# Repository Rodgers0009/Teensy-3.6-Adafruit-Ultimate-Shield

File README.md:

# Teensy-3.6-Adafruit-Ultimate-Shield
Shield for the Teensy 3.6 and Adafruit Ultimate V3 GPS with interactions with all pins on the Teensy

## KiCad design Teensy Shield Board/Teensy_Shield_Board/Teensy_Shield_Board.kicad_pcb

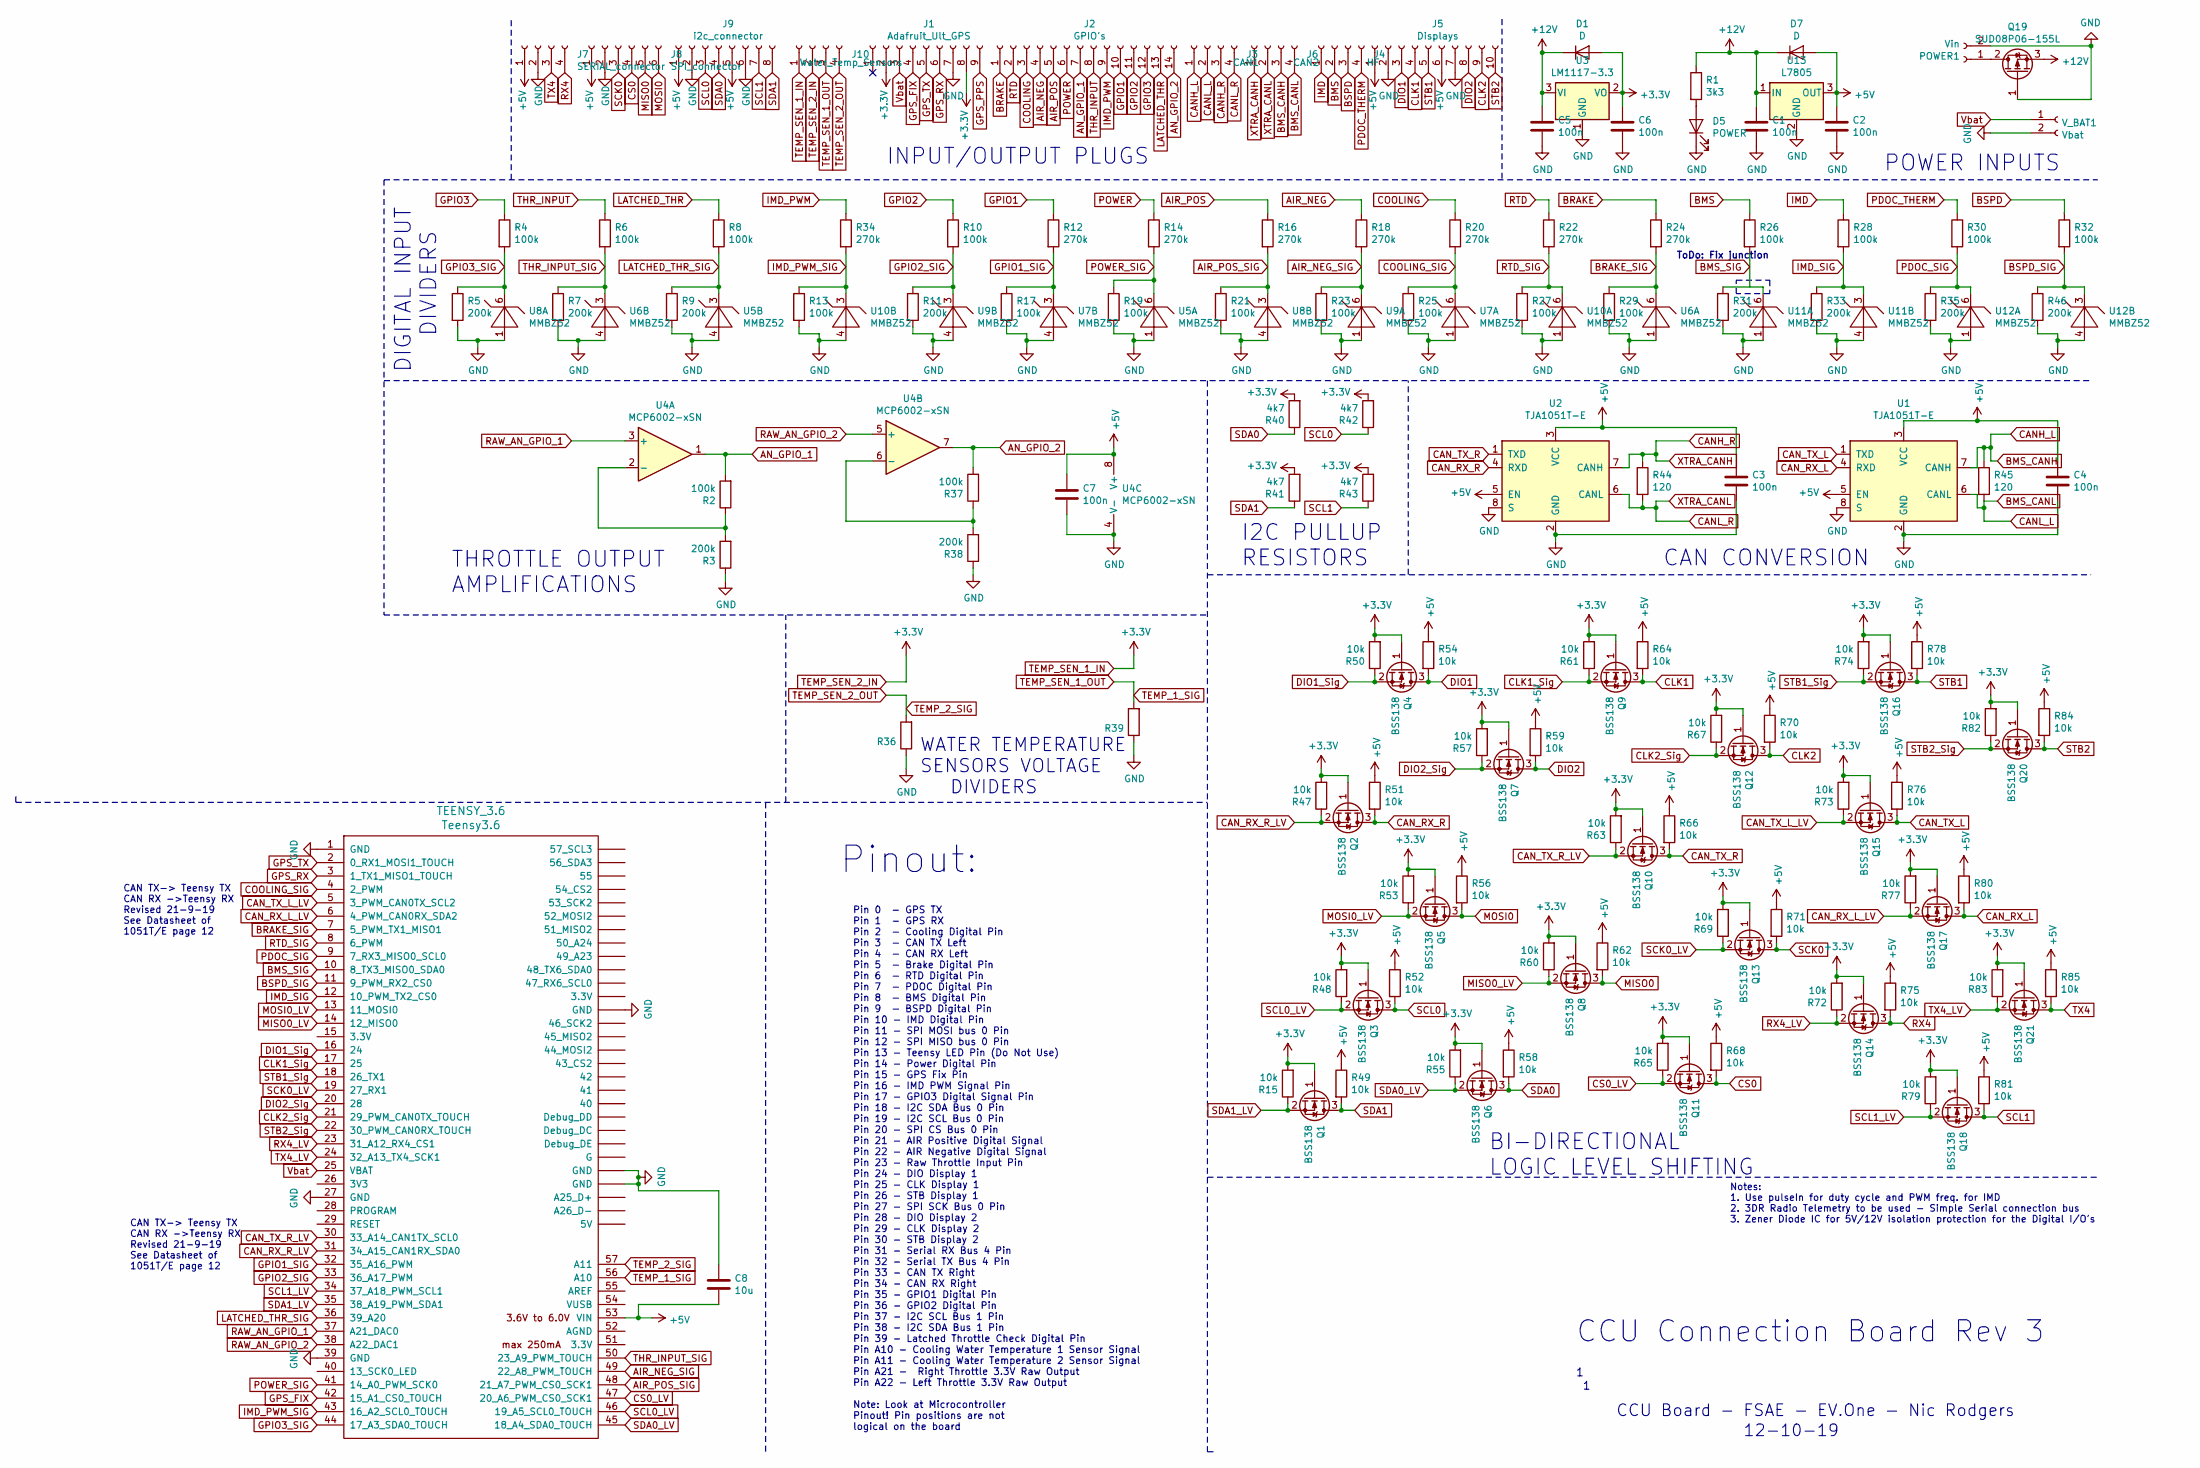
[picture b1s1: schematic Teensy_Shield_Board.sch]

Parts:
C1, C2, C3, C4, C5, C6, C7: 100n; C_0805_2012Metric
C8: 10u; C_0805_2012Metric
D1, D7: D; D_SMA
D5: POWER; LED_0805_2012Metric
J1: Adafruit_Ult_GPS; Adafruit_Ultimate_GPS
J2: GPIO's; Molex-Mini-Fit-Jr-14-pin-P4.2mm-RowP4.2mm
J3: CAN1; Molex-Mini-Fit-Jr-4-pin-P4.2mm-RowP4.2mm
J4: HF; Molex-Mini-Fit-Jr-4-pin-P4.2mm-RowP4.2mm
J5: Displays; Molex-Mini-Fit-Jr-10-pin-P4.2mm-RowP4.2mm
J6: CAN2; Molex-Mini-Fit-Jr-4-pin-P4.2mm-RowP4.2mm
J7: SERIAL_connector; Molex-Mini-Fit-Jr-4-pin-P4.2mm-RowP4.2mm
J8: SPI_connector; Molex-Mini-Fit-Jr-6-pin-P4.2mm-RowP4.2mm
J9: i2c_connector; Molex-Mini-Fit-Jr-8-pin-P4.2mm-RowP4.2mm
J10: Water_Temp_Sensors; Molex-Mini-Fit-Jr-4-pin-P4.2mm-RowP4.2mm
POWER1: Vin; Molex_MiniFit-JR-5556-02A_2x01x4.20mm_Straight
Q1, Q2, Q3, Q4, Q5, Q6, Q7, Q8, Q9, Q10, Q11, Q12, Q13, Q14, Q15, Q16, Q17, Q18, Q20, Q21: BSS138; SOT-23
Q19: SUD08P06-155L; SOT-23
R1: 3k3; R_1206_3216Metric
R2, R4, R6, R8, R10, R13, R17, R19, R21, R23, R25, R26, R27, R28, R29, R30, R32, R37: 100k; R_1206_3216Metric
R3, R5, R7, R9, R11, R31, R33, R35, R38, R46: 200k; R_1206_3216Metric
R12, R14, R16, R18, R20, R22, R24, R34: 270k; R_1206_3216Metric
R15, R47, R48, R49, R50, R51, R52, R53, R54, R55, R56, R57, R58, R59, R60, R61, R62, R63, R64, R65, R66, R67, R68, R69, R70, R71, R72, R73, R74, R75, R76, R77, R78, R79, R80, R81, R82, R83, R84, R85: 10k; R_1206_3216Metric
R36, R39: TO_BE_PROVISIONED; R_1206_3216Metric
R40, R41, R42, R43: 4k7; R_1206_3216Metric
R44, R45: 120; R_1206_3216Metric
TEENSY_3.6: Teensy3.6; Teensy35_36
U1, U2: TJA1051T-E; SOIC-8_3.9x4.9mm_P1.27mm
U3: LM1117-3.3; SOT-223
U4: MCP6002-xSN; SOIC-8_3.9x4.9mm_P1.27mm
U5, U6, U7, U8, U9, U10, U11, U12: MMBZ52; SOT-363_SC-70-6
U13: L7805; TO-263-3_TabPin2
V_BAT1: Vbat; 2032_Batt_holder

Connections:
+5V: C2.1, C3.1, C4.1, C7.1, C8.2, D7.2 (A), J5.1, J5.6, J7.1, J8.1, J9.1, J9.5, R49.1, R51.1, R52.1, R54.1, R56.1, R58.1, R59.1, R62.1, R64.1, R66.1, R68.1, R70.1, R71.1, R75.1, R76.1, R78.1, R80.1, R81.1, R84.1, R85.1, TEENSY_3.6.53 (VIN), U1.3 (VCC), U1.5 (EN), U2.3 (VCC), U2.5 (EN), U4.8 (V+), U13.3 (OUT)
+12V: C1.1, C5.1, D1.1 (K), D7.1 (K), Q19.3 (S), R1.1, U3.3 (VI), U13.1 (IN)
AIR_NEG: J2.4, R18.1
AIR_NEG_SIG: R18.2, R23.1, TEENSY_3.6.49 (22_A8_PWM_TOUCH), U9.6
AIR_POS: J2.5, R16.1
AIR_POS_SIG: R16.2, R21.1, TEENSY_3.6.48 (21_A7_PWM_CS0_SCK1), U8.3
AN_GPIO_1: J2.7, R2.2, U4.1
AN_GPIO_2: J2.14, R37.2, U4.7
BMS: J4.2, R26.1
BMS_CANH: J3.1, J6.3, R45.1, U1.7 (CANH)
BMS_CANL: J3.2, J6.4, R45.2, U1.6 (CANL)
BMS_SIG: R26.2, TEENSY_3.6.10 (8_TX3_MISO0_SDA0)
BRAKE: J2.1, R24.1
BRAKE_SIG: R24.2, R29.1, TEENSY_3.6.7 (5_PWM_TX1_MISO1), U6.6
BSPD: J4.3, R32.1
BSPD_SIG: R32.2, R46.1, TEENSY_3.6.11 (9_PWM_RX2_CS0), U12.3
CANH_R: J3.3, J6.1, R44.1, U2.7 (CANH)
CANL_R: J3.4, J6.2, R44.2, U2.6 (CANL)
CAN_RX_L: Q17.3 (D), R80.2, U1.4 (RXD)
CAN_RX_L_LV: Q17.2 (S), R77.1, TEENSY_3.6.6 (4_PWM_CAN0RX_SDA2)
CAN_RX_R: Q2.3 (D), R51.2, U2.4 (RXD)
CAN_RX_R_LV: Q2.2 (S), R47.1, TEENSY_3.6.31 (34_A15_CAN1RX_SDA0)
CAN_TX_L: Q15.3 (D), R76.2, U1.1 (TXD)
CAN_TX_L_LV: Q15.2 (S), R73.1, TEENSY_3.6.5 (3_PWM_CAN0TX_SCL2)
CAN_TX_R: Q10.3 (D), R66.2, U2.1 (TXD)
CAN_TX_R_LV: Q10.2 (S), R63.1, TEENSY_3.6.30 (33_A14_CAN1TX_SCL0)
CLK1: J5.4, Q9.3 (D), R64.2
CLK1_Sig: Q9.2 (S), R61.1, TEENSY_3.6.17 (25)
CLK2: J5.9, Q12.3 (D), R70.2
CLK2_Sig: Q12.2 (S), R67.1, TEENSY_3.6.21 (29_PWM_CAN0TX_TOUCH)
COOLING: J2.3, R20.1
COOLING_SIG: R20.2, R25.1, TEENSY_3.6.4 (2_PWM), U7.6
CS0: J8.4, Q11.3 (D), R68.2
CS0_LV: Q11.2 (S), R65.1, TEENSY_3.6.47 (20_A6_PWM_CS0_SCK1)
DIO1: J5.3, Q4.3 (D), R54.2
DIO1_Sig: Q4.2 (S), R50.1, TEENSY_3.6.16 (24)
DIO2: J5.8, Q7.3 (D), R59.2
DIO2_Sig: Q7.2 (S), R57.1, TEENSY_3.6.20 (28)
GND: C1.2, C2.2, C3.2, C4.2, C5.2, C6.2, C7.2, C8.1, D5.1 (K), J1.7, J5.2, J5.7, J7.2, J8.2, J9.2, J9.6, POWER1.2, Q19.1 (G), R3.1, R5.2, R7.2, R9.2, R11.2, R13.2, R17.2, R19.2, R21.2, R23.2, R25.2, R27.2, R29.2, R31.2, R33.2, R35.2, R36.1, R38.1, R39.1, R46.2, TEENSY_3.6.1 (GND), TEENSY_3.6.27 (GND), TEENSY_3.6.39 (GND), TEENSY_3.6.~ (3.3V), U1.2 (GND), U1.8 (S), U2.2 (GND), U2.8 (S), U3.1 (GND), U4.4 (V-), U5.1, U5.4, U6.1, U6.4, U7.1, U7.4, U8.1, U8.4, U9.1, U9.4, U10.1, U10.4, U11.1, U11.4, U12.1, U12.4, U13.2 (GND), V_BAT1.2
GPIO1: J2.10, R12.1
GPIO1_SIG: R12.2, R17.1, TEENSY_3.6.32 (35_A16_PWM), U7.3
GPIO2: J2.11, R10.1
GPIO2_SIG: R10.2, R11.1, TEENSY_3.6.33 (36_A17_PWM), U9.3
GPIO3: J2.12, R4.1
GPIO3_SIG: R4.2, R5.1, TEENSY_3.6.44 (17_A3_SDA0_TOUCH), U8.6
GPS_FIX: J1.4, TEENSY_3.6.42 (15_A1_CS0_TOUCH)
GPS_RX: J1.6, TEENSY_3.6.3 (1_TX1_MISO1_TOUCH)
GPS_TX: J1.5, TEENSY_3.6.2 (0_RX1_MOSI1_TOUCH)
IMD: J4.1, R28.1
IMD_PWM: J2.9, R34.1
IMD_PWM_SIG: R13.1, R34.2, TEENSY_3.6.43 (16_A2_SCL0_TOUCH), U10.3
IMD_SIG: R28.2, R33.1, TEENSY_3.6.12 (10_PWM_TX2_CS0), U11.3
LATCHED_THR: J2.13, R8.1
LATCHED_THR_SIG: R8.2, R9.1, TEENSY_3.6.36 (39_A20), U5.3
MISO0: J8.5, Q8.3 (D), R62.2
MISO0_LV: Q8.2 (S), R60.1, TEENSY_3.6.14 (12_MISO0)
MOSI0: J8.6, Q5.3 (D), R56.2
MOSI0_LV: Q5.2 (S), R53.1, TEENSY_3.6.13 (11_MOSI0)
unnamed: D5.2 (A), R1.2
unnamed: POWER1.1, Q19.2 (D)
unnamed: R2.1, R3.2, U4.2 (-)
unnamed: R31.1, U11.6
unnamed: R37.1, R38.2, U4.6 (-)
PDOC_SIG: R30.2, R35.1, TEENSY_3.6.9 (7_RX3_MISO0_SCL0), U12.6
PDOC_THERM: J4.4, R30.1
POWER: J2.6, R14.1
POWER_SIG: R14.2, R19.1, TEENSY_3.6.41 (14_A0_PWM_SCK0), U5.6
RAW_AN_GPIO_1: TEENSY_3.6.37 (A21_DAC0), U4.3 (+)
RAW_AN_GPIO_2: TEENSY_3.6.38 (A22_DAC1), U4.5 (+)
RTD: J2.2, R22.1
RTD_SIG: R22.2, R27.1, TEENSY_3.6.8 (6_PWM), U10.6
RX4: J7.4, Q14.3 (D), R75.2
RX4_LV: Q14.2 (S), R72.1, TEENSY_3.6.23 (31_A12_RX4_CS1)
SCK0: J8.3, Q13.3 (D), R71.2
SCK0_LV: Q13.2 (S), R69.1, TEENSY_3.6.19 (27_RX1)
SCL0: J9.3, Q3.3 (D), R42.1, R52.2
SCL0_LV: Q3.2 (S), R48.1, TEENSY_3.6.46 (19_A5_SCL0_TOUCH)
SCL1: J9.7, Q18.3 (D), R43.1, R81.2
SCL1_LV: Q18.2 (S), R79.1, TEENSY_3.6.34 (37_A18_PWM_SCL1)
SDA0: J9.4, Q6.3 (D), R40.1, R58.2
SDA0_LV: Q6.2 (S), R55.1, TEENSY_3.6.45 (18_A4_SDA0_TOUCH)
SDA1: J9.8, Q1.3 (D), R41.1, R49.2
SDA1_LV: Q1.2 (S), R15.1, TEENSY_3.6.35 (38_A19_PWM_SDA1)
STB1: J5.5, Q16.3 (D), R78.2
STB1_Sig: Q16.2 (S), R74.1, TEENSY_3.6.18 (26_TX1)
STB2: J5.10, Q20.3 (D), R84.2
STB2_Sig: Q20.2 (S), R82.1, TEENSY_3.6.22 (30_PWM_CAN0RX_TOUCH)
TEMP_1_SIG: J10.3, R39.2, TEENSY_3.6.56 (A10)
TEMP_2_SIG: J10.4, R36.2, TEENSY_3.6.57 (A11)
TEMP_SEN_1_IN: C6.1, D1.2 (A), J1.2, J1.8, J10.1, J10.2, Q1.1 (G), Q2.1 (G), Q3.1 (G), Q4.1 (G), Q5.1 (G), Q6.1 (G), Q7.1 (G), Q8.1 (G), Q9.1 (G), Q10.1 (G), Q11.1 (G), Q12.1 (G), Q13.1 (G), Q14.1 (G), Q15.1 (G), Q16.1 (G), Q17.1 (G), Q18.1 (G), Q20.1 (G), Q21.1 (G), R15.2, R40.2, R41.2, R42.2, R43.2, R47.2, R48.2, R50.2, R53.2, R55.2, R57.2, R60.2, R61.2, R63.2, R65.2, R67.2, R69.2, R72.2, R73.2, R74.2, R77.2, R79.2, R82.2, R83.2, U3.2 (VO)
THR_INPUT: J2.8, R6.1
THR_INPUT_SIG: R6.2, R7.1, TEENSY_3.6.50 (23_A9_PWM_TOUCH), U6.3
TX4: J7.3, Q21.3 (D), R85.2
TX4_LV: Q21.2 (S), R83.1, TEENSY_3.6.24 (32_A13_TX4_SCK1)
Vbat: J1.3, TEENSY_3.6.25 (VBAT), V_BAT1.1

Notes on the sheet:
POWER INPUTS
CAN CONVERSION
BI-DIRECTIONAL LOGIC LEVEL SHIFTING
Pinout:
Pin 0 - GPS TX Pin 1 - GPS RX Pin 2 - Cooling Digital Pin Pin 3 - CAN TX Left Pin 4 - CAN RX Left Pin 5 - Brake Digital Pin Pin 6 - RTD Digital Pin Pin 7 - PDOC Digital Pin Pin 8 - BMS Digital Pin Pin 9 - BSPD Digital Pin Pin 10 - IMD Digital Pin Pin 11 - SPI MOSI bus 0 Pin Pin 12 - SPI MISO bus 0 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
CCU Connection Board Rev 3
CCU Board - FSAE - EV.One - Nic Rodgers
12-10-19
CAN TX-> Teensy TX CAN RX ->Teensy RX Revised 21-9-19 See Datasheet of 1051T/E page 12
DIGITAL INPUT DIVIDERS
INPUT/OUTPUT PLUGS
Notes: 1. Use pulseIn for duty cycle and PWM freq. for IMD 2. 3DR Radio Telemetry to be used - Simple Serial connection bus 3. Zener Diode IC for 5V/12V isolation protection for the Digital I/O's
I2C PULLUP RESISTORS
THROTTLE OUTPUT AMPLIFICATIONS
WATER TEMPERATURE SENSORS VOLTAGE DIVIDERS
ToDo: Fix junction

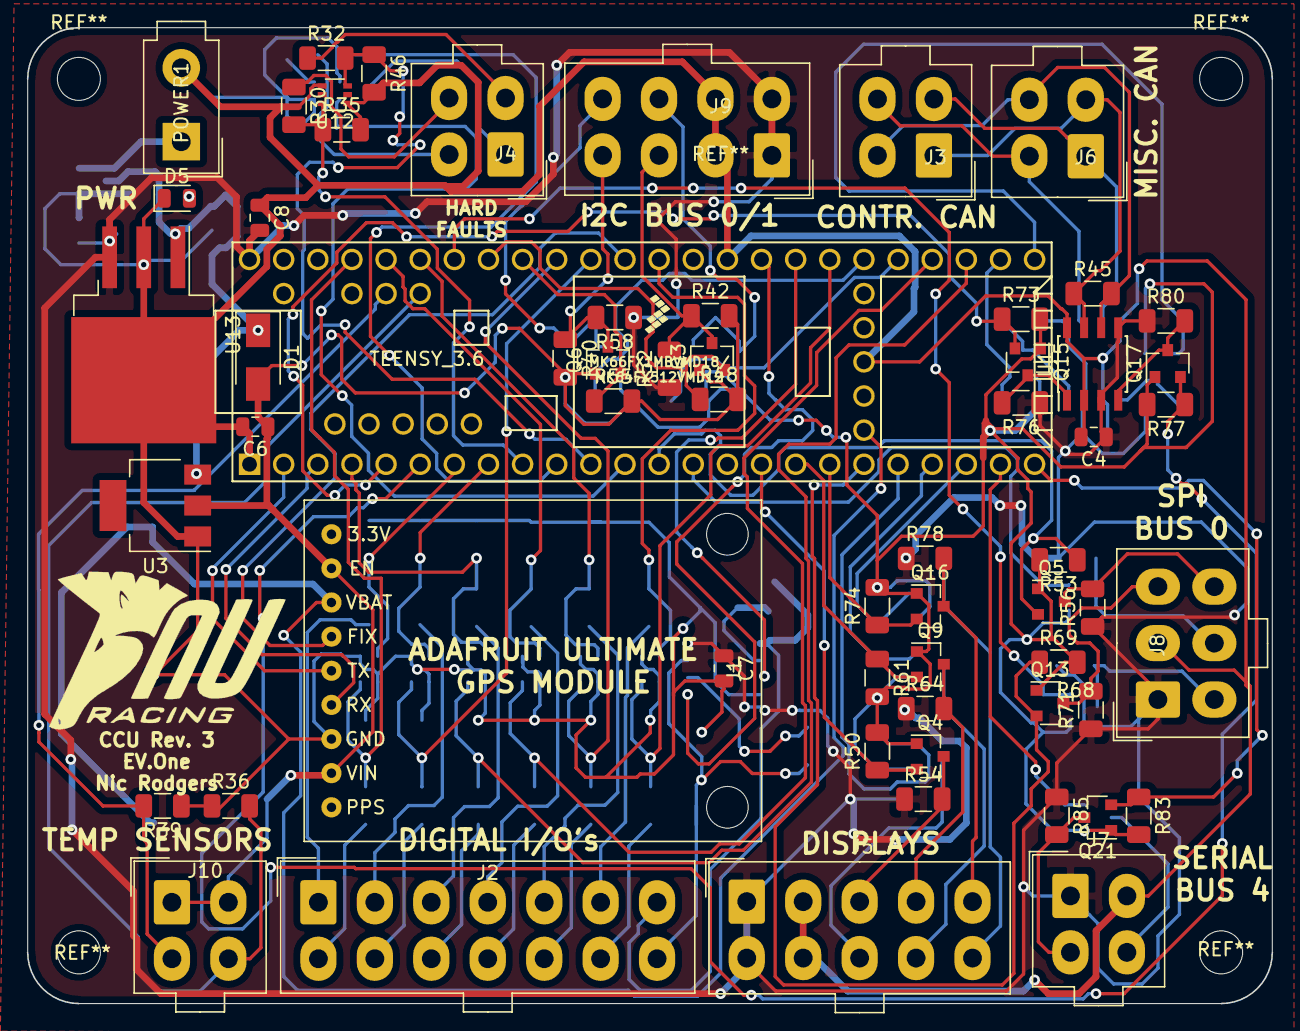
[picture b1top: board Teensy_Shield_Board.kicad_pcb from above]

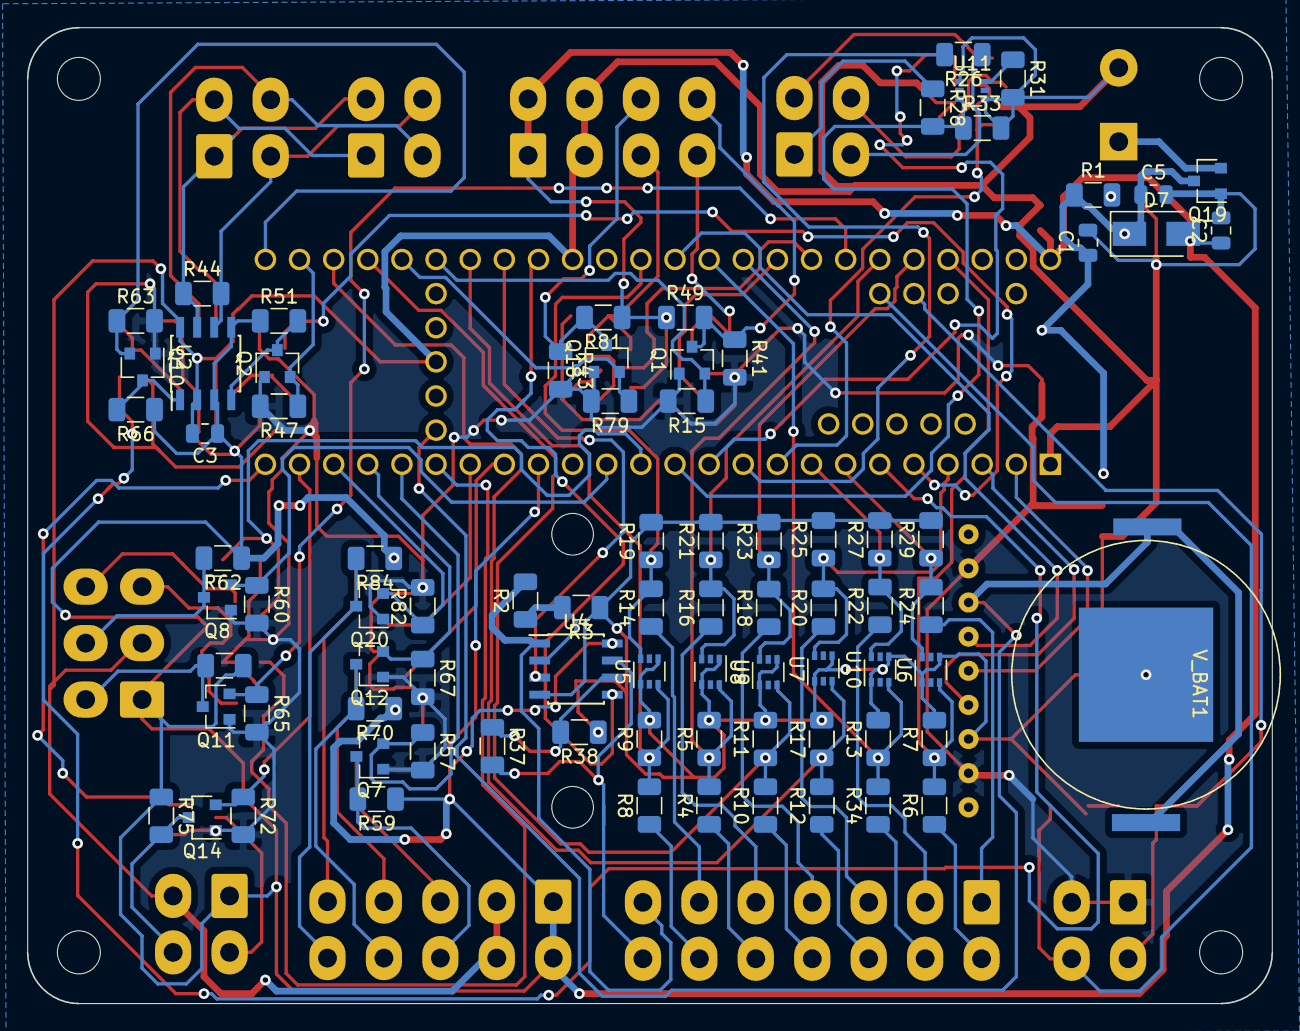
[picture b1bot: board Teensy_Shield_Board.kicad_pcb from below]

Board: 2 copper layers, 92.6 x 72.6 mm, 143 parts (82 on the bottom side), 95 nets.

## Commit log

2019-11-08 no message
